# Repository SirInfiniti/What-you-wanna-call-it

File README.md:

**Hackpad!**

A miniature keyboard to assist in all your needs, using KiCAD, Fusion, and KMK.

**Screenshots:**

My Schematic:

My PCB: 

My Case: 

Final Project:

**Bill of Materials:**

1. 1 x JLCPCP Manufacturing PCB
2. 9 x Cherry MX Switches
3. 1 x Xiao RP2040 microcontrollers
4. 1x 0.91" OLED Display
5. 1 x Custom PCB
6. 9 x Cherry MX Keycaps
7. 4 x Screws
8. 4 x Heatset Inserts
9. 1 x 3d Printed Case

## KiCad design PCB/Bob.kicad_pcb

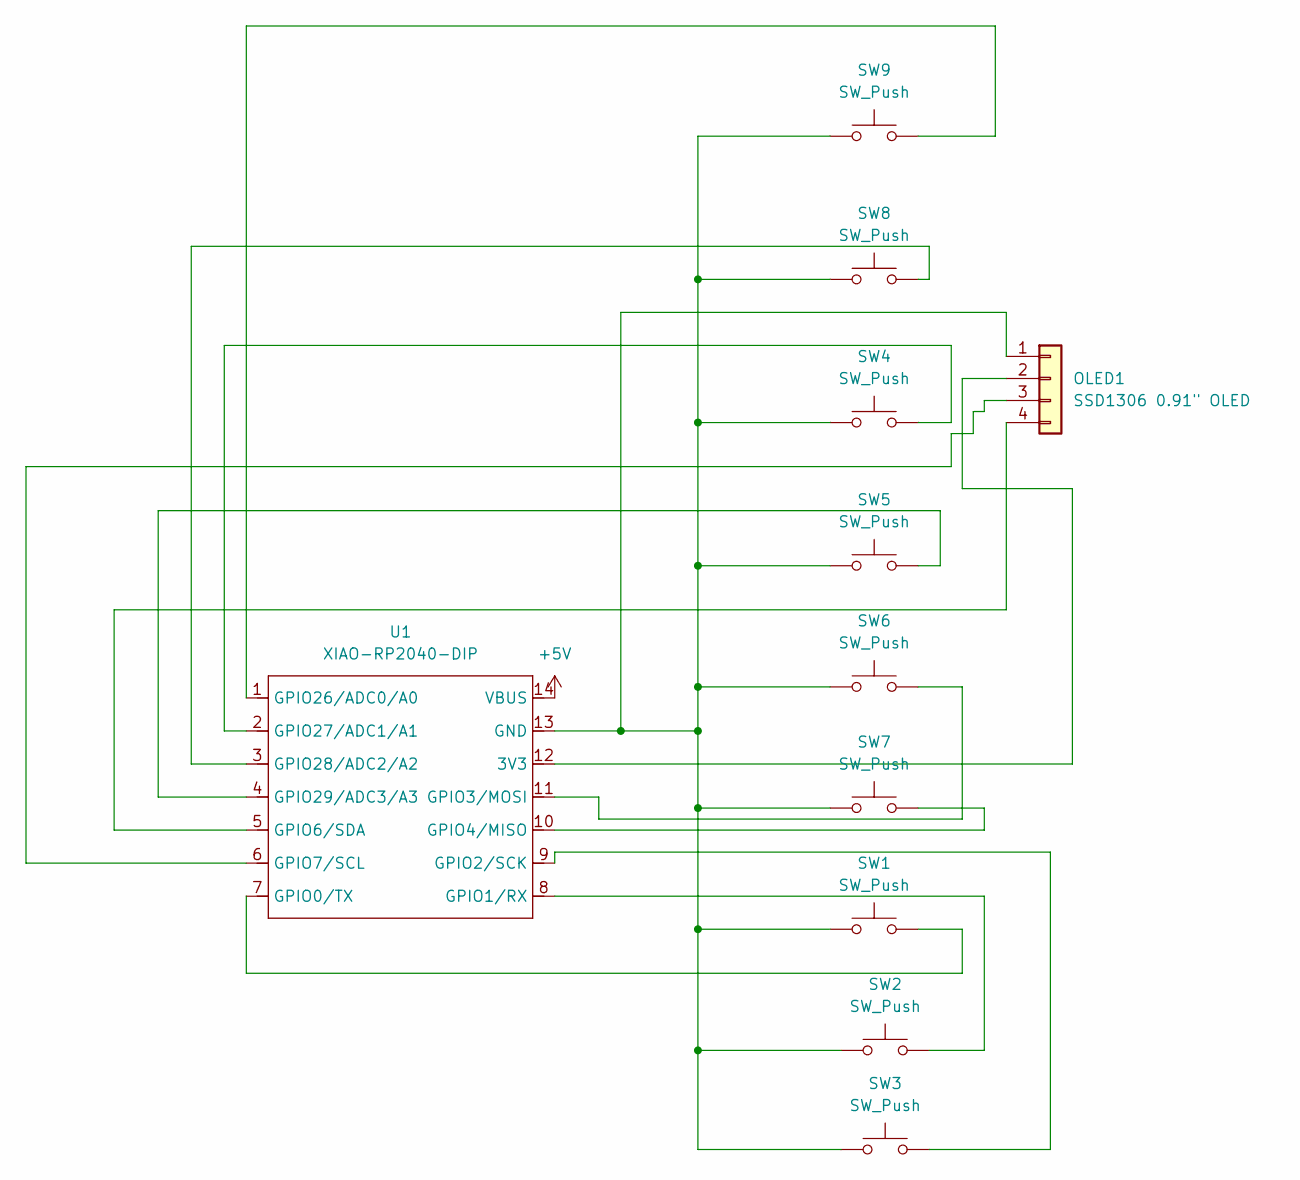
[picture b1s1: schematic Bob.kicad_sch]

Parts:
OLED1: SSD1306 0.91" OLED; SSD1306-0.91-OLED-4pin-128x32
SW1, SW2, SW3, SW4, SW5, SW6, SW7, SW8, SW9: SW_Push; SW_Cherry_MX_1.00u_PCB
U1: XIAO-RP2040-DIP

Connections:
+5V: U1.14 (VBUS)
unnamed: OLED1.1, SW1.1, SW2.1, SW3.1, SW4.1, SW5.1, SW6.1, SW7.1, SW8.1, SW9.1, U1.13 (GND)
unnamed: OLED1.2, U1.12 (3V3)
unnamed: OLED1.3, U1.6 (GPIO7/SCL)
unnamed: OLED1.4, U1.5 (GPIO6/SDA)
unnamed: SW1.2, U1.7 (GPIO0/TX)
unnamed: SW2.2, U1.8 (GPIO1/RX)
unnamed: SW3.2, U1.9 (GPIO2/SCK)
unnamed: SW6.2, U1.11 (GPIO3/MOSI)
unnamed: SW7.2, U1.10 (GPIO4/MISO)
unnamed: SW9.2, U1.1 (GPIO26/ADC0/A0)
unnamed: SW4.2, U1.2 (GPIO27/ADC1/A1)
unnamed: SW8.2, U1.3 (GPIO28/ADC2/A2)
unnamed: SW5.2, U1.4 (GPIO29/ADC3/A3)

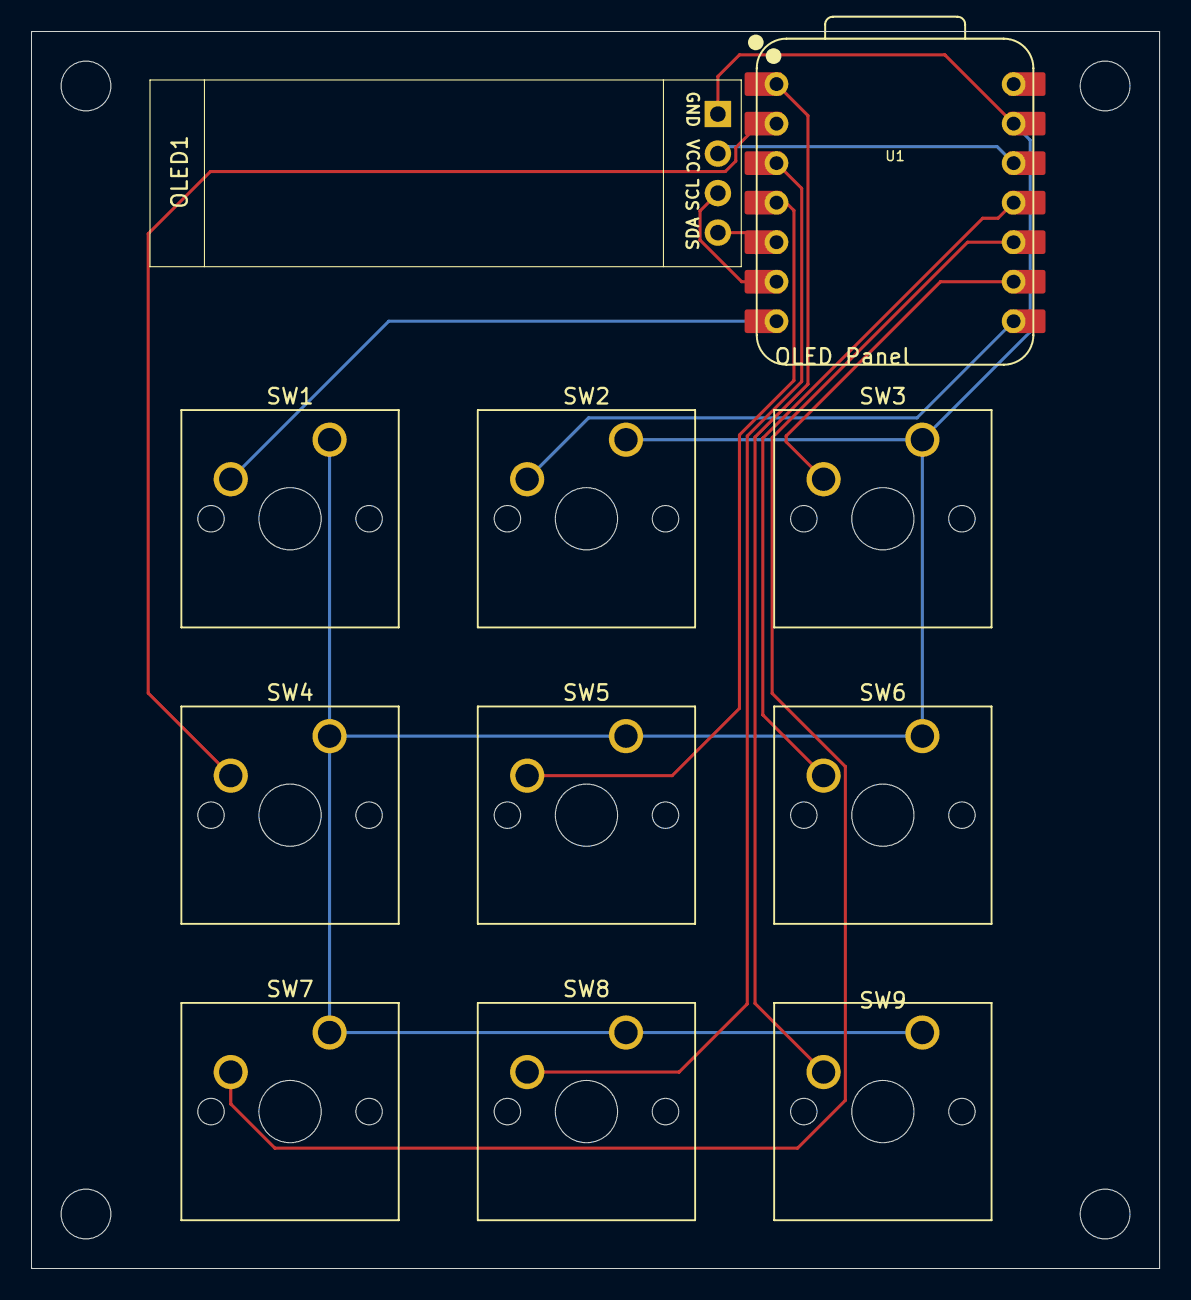
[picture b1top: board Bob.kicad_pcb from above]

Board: 2 copper layers, 72.5 x 79.5 mm, 11 parts (0 on the bottom side), 13 nets.

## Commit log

2025-12-19 Added local files
2025-12-19 Added firmware
